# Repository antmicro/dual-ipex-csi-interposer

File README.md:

# Dual I-PEX CSI Interposer

Copyright (c) 2022-2023 [Antmicro](https://www.antmicro.com)

## Overview

This repository contains open hardware design files for the Dual I-PEX micro-coaxial CSI Interposer.
The board serves as a 2-to-1 CSI-2 camera cable adapter.

It features two 30-pin I-PEX camera connectors with a 4-lane MIPI CSI-2 interface, I2C and power supply as well as a single upstream connector - 50-pin FFC, compatible with video processing boards created by Antmicro such as:

* [TX2 Deep Learning Platform](https://github.com/antmicro/jetson-tx2-deep-learning-platform) supporting NVIDIA Jetson TX2 
* [AGX CSI Adapter](https://github.com/antmicro/jetson-nano-baseboard) supporting NVIDIA Jetson Xavier AGX and NVIDIA Jetson Orin AGX
* [Jetson Nano Baseboard](https://github.com/antmicro/jetson-nano-baseboard) supporting NVIDIA Jetson Nano, Jetson Xavier NX, Jetson TX2 NX
* [AMD-Xilinx Kria K26 Devboard](https://github.com/antmicro/kria-k26-devboard)
* [Antmicro's Snapdragon 625 baseboard](https://github.com/antmicro/snapdragon-625-baseboard)
* [Antmicro's Snapdragon 845 baseboard](https://github.com/antmicro/snapdragon-845-baseboard)

## Repository structure

The main repository directory contains KiCad PCB project files, a [LICENSE](LICENSE), and a README.
The remaining files are stored in the following directories:

* `lib` - contains the component libraries,
* `doc` - contains the adapter [schematics](doc/dual-ipex-csi-interposer.pdf),
* `img` - contains the board visualization.

## Key features

* 50-pin dual MIPI CSI-2 FFC connector (host side),
* twin 30-wire I-PEX micro coax CSI-2 connectors (camera side) (interface compatible with the [Framos CSI Adapter](https://github.com/antmicro/framos-csi-adapter)),
* 4-lane MIPI CSI-2 per camera.

## License

This project is published under the [Apache-2.0](LICENSE) license.

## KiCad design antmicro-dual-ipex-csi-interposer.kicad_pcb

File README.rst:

============
Dual Ipex CSI Interposer
============

Copyright (c) 2018-2022 `Antmicro <https://www.antmicro.com>`_

.. figure:: img/antmicro-dual-ipex-csi-interposer-top.png

Overview
--------

This repository contains open hardware design files for an Dual Ipex CSI Interposer.
(add description here)
The design files were prepared in KiCad 6.

Repository structure
--------------------
The main repository directory contains KiCad PCB project files, a LICENSE and README.
The remaining files are stored in the following directories:

* ``lib`` - contains the component libraries
* ``img`` - contains graphics for this README

License
=======

`Apache-2.0 <LICENSE>`_

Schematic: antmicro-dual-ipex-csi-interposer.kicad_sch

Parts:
C1, C2: C_100n_0402; 0402-cap; MPN GRM155R61H104KE14D
J1: WE_68715014522; MPN 68715014522
J2, J3: MSAK24025P30; MPN MSAK24025P30
MP1, MP2, MP3, MP4: PCB_Mount_Hole_2.2_4.5; mounting-hole-2.2mm
N1: oshw_logo; oshw-logo
N2: antmicro_logo; antmicro-logo_scaled_12mm
R1, R2, R3, R4, R5, R6, R7, R8: R_0R_0402; 0402-res; MPN ERJ2GE0R00X
TP1, TP2, TP3, TP4, TP5, TP6, TP7, TP8, TP9, TP10: TP_SMD1MM; Testpoint_smd_1mm

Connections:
3V3_FFC: C1.1, J1.47, J1.48, J2.24, J2.25, J2.26, J3.24, J3.25, J3.26
5V0_SYS: C2.1, J1.49, J1.50, J2.27, J2.28, J2.29, J2.30, J3.27, J3.28, J3.29, J3.30
/CAM_CSI_CAM_EN: J1.32, R5.2, R6.2, TP7.1
/CAM_CSI_CAM_XVS: J1.34, R7.2, R8.2, TP8.1
/CAM_L_SCL: J1.40, R3.2, TP4.1
/CAM_L_SDA: J1.39, R4.2, TP3.1
/CAM_R_SCL: J1.42, R1.2, TP5.1
/CAM_R_SDA: J1.41, R2.2, TP6.1
CAM1_CSI_CAM_CLK: J2.22, TP1.1
CAM1_CSI_CAM_EN: J2.20, R6.1
CAM1_CSI_CAM_XTRIG: J2.23, TP2.1
CAM1_CSI_CAM_XVS: J2.21, R8.1
CAM1_CSI_CLK_N: J1.28, J2.14
CAM1_CSI_CLK_P: J1.29, J2.15
CAM1_CSI_D0_N: J1.25, J2.11
CAM1_CSI_D0_P: J1.26, J2.12
CAM1_CSI_D1_N: J1.23, J2.8
CAM1_CSI_D1_P: J1.24, J2.9
CAM1_CSI_D2_N: J1.21, J2.5
CAM1_CSI_D2_P: J1.22, J2.6
CAM1_CSI_D3_N: J1.19, J2.2
CAM1_CSI_D3_P: J1.20, J2.3
CAM1_SCL: J2.18, R1.1
CAM1_SDA: J2.17, R2.1
CAM2_CSI_CAM_CLK: J3.22, TP9.1
CAM2_CSI_CAM_EN: J3.20, R5.1
CAM2_CSI_CAM_XTRIG: J3.23, TP10.1
CAM2_CSI_CAM_XVS: J3.21, R7.1
CAM2_CSI_CLK_N: J1.10, J3.14
CAM2_CSI_CLK_P: J1.11, J3.15
CAM2_CSI_D0_N: J1.7, J3.11
CAM2_CSI_D0_P: J1.8, J3.12
CAM2_CSI_D1_N: J1.5, J3.8
CAM2_CSI_D1_P: J1.6, J3.9
CAM2_CSI_D2_N: J1.3, J3.5
CAM2_CSI_D2_P: J1.4, J3.6
CAM2_CSI_D3_N: J1.1, J3.2
CAM2_CSI_D3_P: J1.2, J3.3
CAM2_SCL: J3.18, R3.1
CAM2_SDA: J3.17, R4.1
GND: C1.2, C2.2, J1.9, J1.12, J1.15, J1.18, J1.27, J1.30, J2.1, J2.4, J2.7, J2.10, J2.13, J2.16, J2.19, J3.1, J3.4, J3.7, J3.10, J3.13, J3.16, J3.19

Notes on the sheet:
CAM_L_D1_P
CAM_L_SDA
CSI_E_CLK_N
CSI_E_CLK_P
CAM_L_D2_P
CAM_R_SCL
Matching cable: KAB-I-PEX-20453-030T-0500-1:1-ROUND
Pull ups on I2C might be set to 3V3 or 1V8 on JNB 3V3 is default configuration
CAM_L_D0_N
CSI_F_D0_P
Text
CSI_R_D0_P
CAM_L_D0_P
CAM_L_D1_N
Framos CSI interposer
CSI_R_D1_P
CAM_L_CLK_P
CSI_R_D1_N
J6-GPIO13 pin 228/J7-CAM0_PWDN pin 114 (Nano)
Mount holes
Matching socket: STE-I-PEX-20455-030E-12
CAM_L_D3_P
CAM_R_SDA
LEFT CAMERA
CAM_L_CLK_N
CSI_F_D1_P
J6-GPIO11 pin 216/J7-GPIO06 pin 130 (Nano)
Framos CSI adapter connectors
RIGHT CAMERA
CSI_R_D0_N
Logotypes
CSI_F_D0_N
CAM_L_D3_N
Jetson nano baseboard CSI connector
CAM_L_D2_N
CSI_F_D1_N
CAM_L_SCL

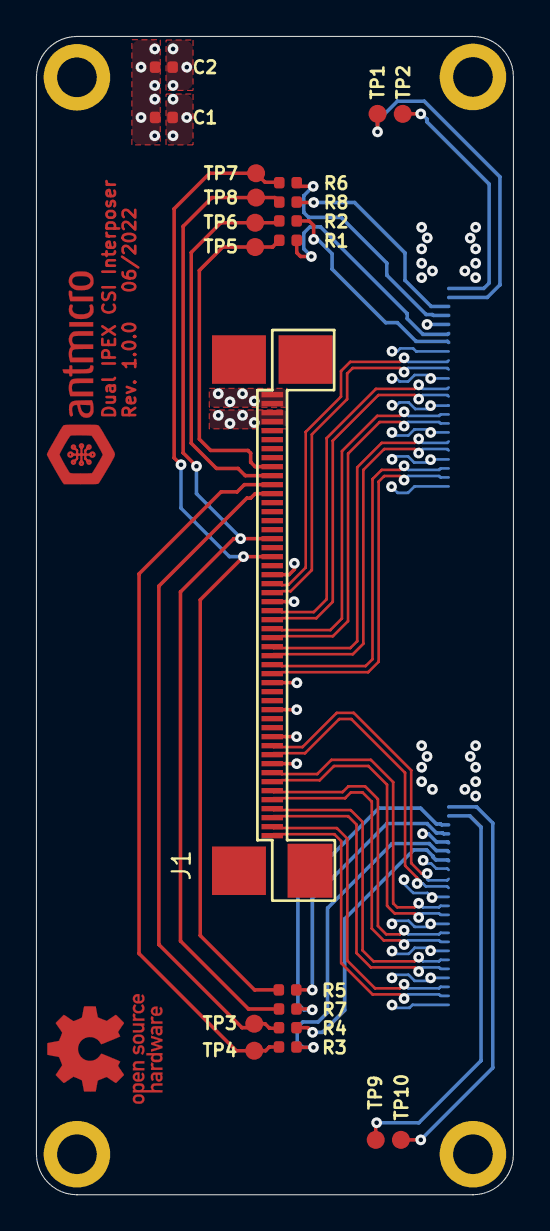
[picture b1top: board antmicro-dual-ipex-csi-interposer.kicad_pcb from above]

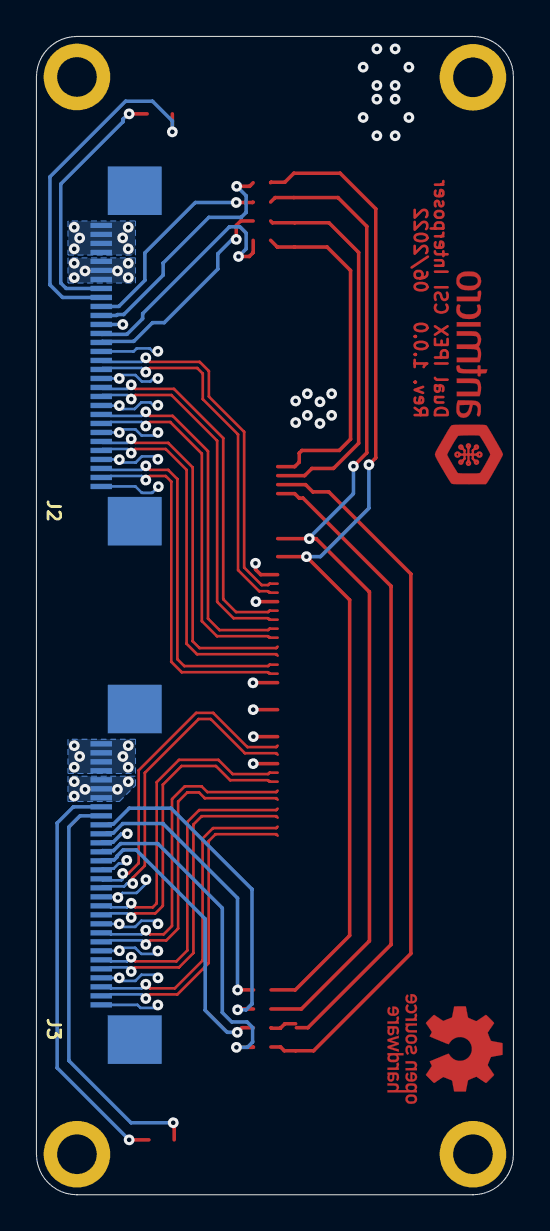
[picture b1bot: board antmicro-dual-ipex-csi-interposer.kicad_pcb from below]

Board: 4 copper layers, 26.5 x 64.3 mm, 29 parts (2 on the bottom side), 41 nets.

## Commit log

2022-07-28 Initial commit. Add single IPEX
    Fix library issue
2022-07-28 Add second connector and assigned signals
    Remove Kicad5 CI
2022-07-28 Complete schematic. Proceed PCB layout
2022-07-28 Route low speed, optimize polygons, match lane length
2022-07-28 Add decoupling, move all TP to the top
    Cosmetic changes
    Capital letter fix
2022-07-28 Generate loclib. Cleanup
    Add boards image. Add image link to README
2022-10-19 Edit README
2022-10-19 Update schematic PDF
2022-10-19 README: fix img path
2022-10-19 README: fix SCH path
2022-10-19 Notes added by 'git notes add'
2023-01-19 README: review
2023-02-08 Minor review of README
2023-03-30 README: update license string
